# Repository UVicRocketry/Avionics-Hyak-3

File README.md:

# Avionics-Hyak-3

This is a file to contain all schematic and PCB related information, as well as any corresponding datasheets, for the Hyak-3 Avionics systems.

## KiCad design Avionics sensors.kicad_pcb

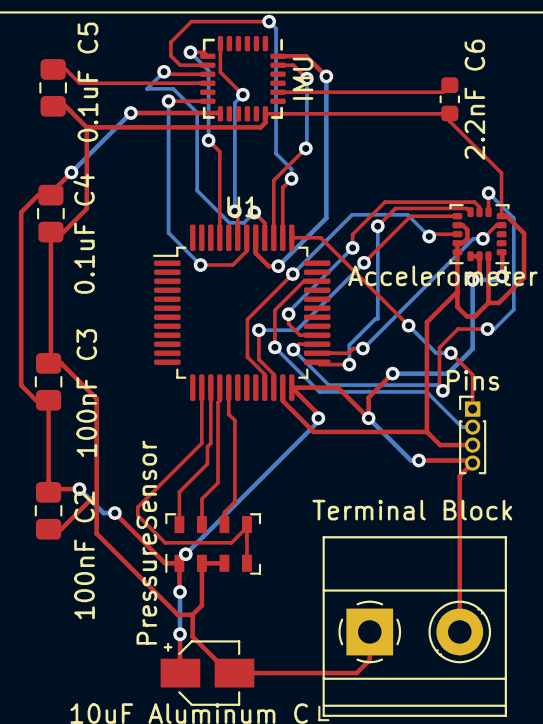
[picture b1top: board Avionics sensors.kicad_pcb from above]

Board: 2 copper layers, 12 parts (0 on the bottom side), 23 nets.

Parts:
0.1uF C4, 0.1uF C5: 0.1uF; C_0805_2012Metric_Pad1.15x1.40mm_HandSolder
2.2nF C6: 2.2nF; C_0603_1608Metric
10uF Aluminum C: 10uF; CP_Elec_3x5.3
100nF C2, 100nF C3: 100nF; C_0805_2012Metric_Pad1.15x1.40mm_HandSolder
Accelerometer: LIS331HH; LGA-16_3x3mm_P0.5mm_LayoutBorder3x5y
IMU: MPU-6000; InvenSense_QFN-24_4x4mm_P0.5mm
Pins: PinHeader_1x04_P1.00mm_Vertical
PressureSensor: MS5607-02BA; LGA-8_3x5mm_P1.25mm
Terminal Block: TerminalBlock_Phoenix_MKDS-1,5-2_1x02; TerminalBlock_Phoenix_MKDS-1,5-2_1x02_P5.00mm_Horizontal
U1: STM32L151CCTx; LQFP-48_7x7mm_P0.5mm

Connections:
+3V3: 0.1uF C4.1, 10uF Aluminum C.1, 100nF C2.1, 100nF C3.1, Accelerometer.1, Accelerometer.14, Accelerometer.15, IMU.13, Pins.4, PressureSensor.1, Terminal Block.2, U1.24
/IMU-CS: IMU.8, U1.38
/PS-CSB: PressureSensor.4, PressureSensor.5, U1.14
/PS-SDI: PressureSensor.7, U1.16
/PS-SDO: PressureSensor.6, U1.17
/PS-SPICLK: PressureSensor.8, U1.15
GND: 0.1uF C4.2, 0.1uF C5.2, 2.2nF C6.2, 10uF Aluminum C.2, 100nF C2.2, 100nF C3.2, Accelerometer.5, Accelerometer.10, Accelerometer.12, Accelerometer.13, Accelerometer.16, IMU.18, Pins.3, PressureSensor.2, PressureSensor.3, Terminal Block.1, U1.23
unnamed: Accelerometer.4, U1.26
unnamed: Accelerometer.6, U1.27
unnamed: Accelerometer.7, U1.28
unnamed: Accelerometer.8, U1.25
unnamed: Accelerometer.9, U1.22
unnamed: Accelerometer.11, U1.21
unnamed: 0.1uF C5.1, IMU.10
unnamed: 2.2nF C6.1, IMU.20
unnamed: Pins.2, U1.34
unnamed: Pins.1, U1.37
unnamed: IMU.23, U1.39
unnamed: IMU.9, U1.40
unnamed: IMU.24, U1.41
unnamed: IMU.12, U1.42
unnamed: IMU.6, U1.43
unnamed: IMU.7, U1.45

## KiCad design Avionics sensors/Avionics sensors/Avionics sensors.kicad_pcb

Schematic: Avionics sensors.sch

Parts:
Accelerometer1: LIS331HH; LGA-16_3x3mm_P0.5mm_LayoutBorder3x5y
C4, C5: 0.1uF; C_0805_2012Metric_Pad1.15x1.40mm_HandSolder
C6: 2.2nF; C_0805_2012Metric_Pad1.15x1.40mm_HandSolder
C-Aluminum1: 10uF; CP_Elec_3x5.3
C-Ceramic1, C-Ceramic2: 100nF; C_0805_2012Metric_Pad1.15x1.40mm_HandSolder
PressureSensor1: MS5607-02BA; LGA-8_3x5mm_P1.25mm
U1: STM32L151CCTx; LQFP-48_7x7mm_P0.5mm
U2: MPU-6000; InvenSense_QFN-24_4x4mm_P0.5mm

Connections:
+3V3: Accelerometer1.1 (Vdd), Accelerometer1.14 (Vdd), Accelerometer1.15 (Vdd), C4.1, C-Aluminum1.1, C-Ceramic1.1, C-Ceramic2.1, PressureSensor1.1 (VDD), U1.24 (VDD), U2.13
/IMU-CS: U1.38 (PA15), U2.8
/PS-CSB: PressureSensor1.4 (CSB), PressureSensor1.5 (CSB), U1.14 (PA4)
/PS-SDI: PressureSensor1.7 (SDI/SDA), U1.16 (PA6)
/PS-SDO: PressureSensor1.6 (SDO), U1.17 (PA7)
/PS-SPICLK: PressureSensor1.8 (SCLK), U1.15 (PA5)
GND: Accelerometer1.5 (GND), Accelerometer1.10 (GND), Accelerometer1.12 (GND), Accelerometer1.13 (GND), Accelerometer1.16 (GND), C4.2, C5.2, C6.2, C-Aluminum1.2, C-Ceramic1.2, C-Ceramic2.2, PressureSensor1.2 (PS), PressureSensor1.3 (GND), U1.23 (VSS), U2.18
unnamed: Accelerometer1.4 (SCL/SPC), U1.26 (PB13)
unnamed: Accelerometer1.6 (SDA/SDI), U1.27 (PB14)
unnamed: Accelerometer1.7 (SA0/SDO), U1.28 (PB15)
unnamed: Accelerometer1.8 (~CS), U1.25 (PB12)
unnamed: Accelerometer1.9 (INT2), U1.22 (PB11)
unnamed: Accelerometer1.11 (INT1), U1.21 (PB10)
unnamed: C5.1, U2.10
unnamed: C6.1, U2.20
unnamed: U1.39 (PB3), U2.23
unnamed: U1.40 (PB4), U2.9
unnamed: U1.41 (PB5), U2.24
unnamed: U1.42 (PB6), U2.12
unnamed: U1.43 (PB7), U2.6
unnamed: U1.45 (PB8), U2.7

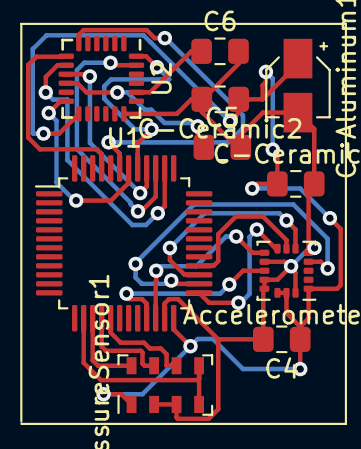
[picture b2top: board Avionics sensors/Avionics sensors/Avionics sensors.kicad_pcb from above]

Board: 2 copper layers, 10 parts (0 on the bottom side), 21 nets.

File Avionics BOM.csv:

"Id";"Designator";"Package";"Quantity";"Designation";"Supplier and ref";
1;"REF**";"PinHeader_1x04_P1.00mm_Vertical";1;"PinHeader_1x04_P1.00mm_Vertical";;;
2;"REF**";"TerminalBlock_MetzConnect_360272_1x01_Horizontal_ScrewM2.6";1;"TerminalBlock_MetzConnect_360272_1x01_Horizontal_ScrewM2.6";;;
3;"U2";"InvenSense_QFN-24_4x4mm_P0.5mm";1;"MPU-6000";;;
4;"U1";"LQFP-48_7x7mm_P0.5mm";1;"STM32L151CCTx";;;
5;"PressureSensor1";"LGA-8_3x5mm_P1.25mm";1;"MS5607-02BA";;;
6;"C-Ceramic2,C-Ceramic1";"C_0805_2012Metric_Pad1.15x1.40mm_HandSolder";2;"100nF";;;
7;"C-Aluminum1";"CP_Elec_3x5.3";1;"10uF";;;
8;"C6";"C_0805_2012Metric_Pad1.15x1.40mm_HandSolder";1;"2.2nF";;;
9;"C5,C4";"C_0805_2012Metric_Pad1.15x1.40mm_HandSolder";2;"0.1uF";;;
10;"Accelerometer1";"LGA-16_3x3mm_P0.5mm_LayoutBorder3x5y";1;"LIS331HH";;;

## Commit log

2020-06-29 Add design files and .gitignore
2020-09-06 Create Avionics Sensors Updated files
